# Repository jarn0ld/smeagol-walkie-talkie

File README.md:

smeagol-walkie-talkie
=====================

Welcome to Audio Group of SMEAGOL Project 2014 the Small, Embedded, Advanced and Generic Objects Laboratory at RWTH Aachen University. 

## Introduction ##

The goal of this project is to stream voice over a radio link. This includes voice recording, voice transmission and playback.
As radio nodes telosb´s needed to be used. This nodes are pretty power full battery powered devices including a micro-controller, a 2.4GHz radio transceiver and some sensors. 

## Hardware ##

Besides the two telosb´s some hardware was required to condition the microphone signal and to amplifie the output signal so that it can be used to drive earphones or a speaker.

### Microphone Amplifier ###

To generate electrical signals out out of sound waves a microphone is needed. For our purposes a electret microphone is right choice because of its small dimensions, its small price and
its good usability. However, the electrical signal generated by the microphone is ways to small for the telosb`s ADC. Therefore, the signal needs to be amplified to match up with the dynamic range
of the ADC. In order to do so we used an OpAmp as an amplifier in negative feedback configuration.  However before amplification the microphone needs to be biased through resistor R1. After amplification it is important to introduce a band limitation in order to satisfy Nyquist's theorem.
Therefore, a low pass is formed by R4 and C4 with a cut cuff below 4kHz.

#### Things to Notice ####
As this board circuit will be mounted directly beneath the transmitting node it is very important to be aware of the radio interference. Therefore, a proper ground plane is a must have, signal lines should be as short as possible and all supply pins should be closely decoupled.   

### Audio Amplifier ###

## Software ##
The program reads the ADC input (10 kHz and 12 bit) and send it over the radio using the CC2420 (RF chip). Afterwards, the sent samples are outputted at the DAC on the receiver seide.

Data flow of the samples:

Sender: ADC->DMA->Buffer->CC2420

Receiver: CC2420->Buffer->DMA->DAC

The code consists of 5 main components:

adc.c and dac.c:

- handles the initialization of the ADC/DAC using a timer

- sampling rate: 10 kHz, 12 bit

dma.c:

- configures the DMA Controller to interact with the ADC/DAC.

- includes the interrupts that are triggered, when a sample buffer was completely filled or outputted

rf.c:

- handles the initialization of the SPI interface, which is required to communite with the CC2420

- initializes the CC2420 (configuring registers)
		 - handles the sending and receiving of packets

main.c:

- puts all components together

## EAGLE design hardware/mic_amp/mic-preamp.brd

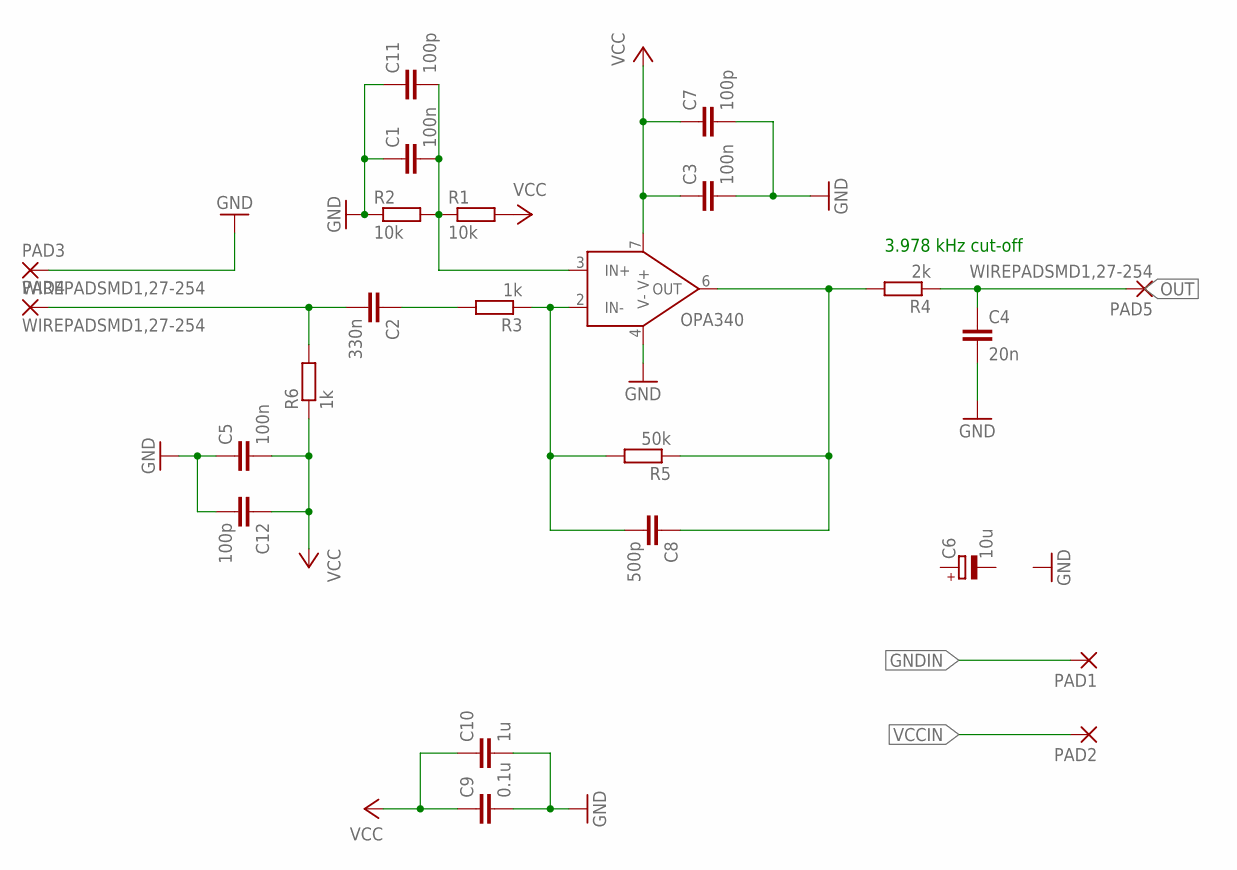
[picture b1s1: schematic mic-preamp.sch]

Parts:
C1, C3, C5: 100n; C0805
C2: 330n; C0805
C4: 20n; C0805
C6: 10u; E2,5-6E
C7, C11, C12: 100p; C0805
C8: 500p; C0805
C9: 0.1u; C0805
C10: 1u; C0805
OPA340: OPA340; DIL08
PAD1, PAD2: WIREPADSMD2,54-5,08; SMD2,54-5,08
PAD3, PAD4, PAD5: WIREPADSMD1,27-254; SMD1,27-2,54
R1, R2: 10k; R0805
R3, R6: 1k; R0805
R4: 2k; R0805
R5: 50k; R0805

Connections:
GND: C1.1, C3.2, C4.2, C5.1, C7.2, C9.2, C10.2, C11.1, C12.2, OPA340.4 (V-), PAD3.1, R2.1
GNDIN: PAD1.1
MIC: C2.2, PAD4.1, R6.2
unnamed: C8.1, OPA340.6 (OUT), R4.2, R5.1
unnamed: C1.2, C11.2, OPA340.3 (IN+), R1.1, R2.2
unnamed: C2.1, R3.2
unnamed: C8.2, OPA340.2 (IN-), R3.1, R5.2
OUT: C4.1, PAD5.1, R4.1
VCC: C3.1, C5.2, C7.1, C9.1, C10.1, C12.1, OPA340.7 (V+), R1.2, R6.1
VCCIN: PAD2.1

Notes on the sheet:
3.978 kHz cut-off

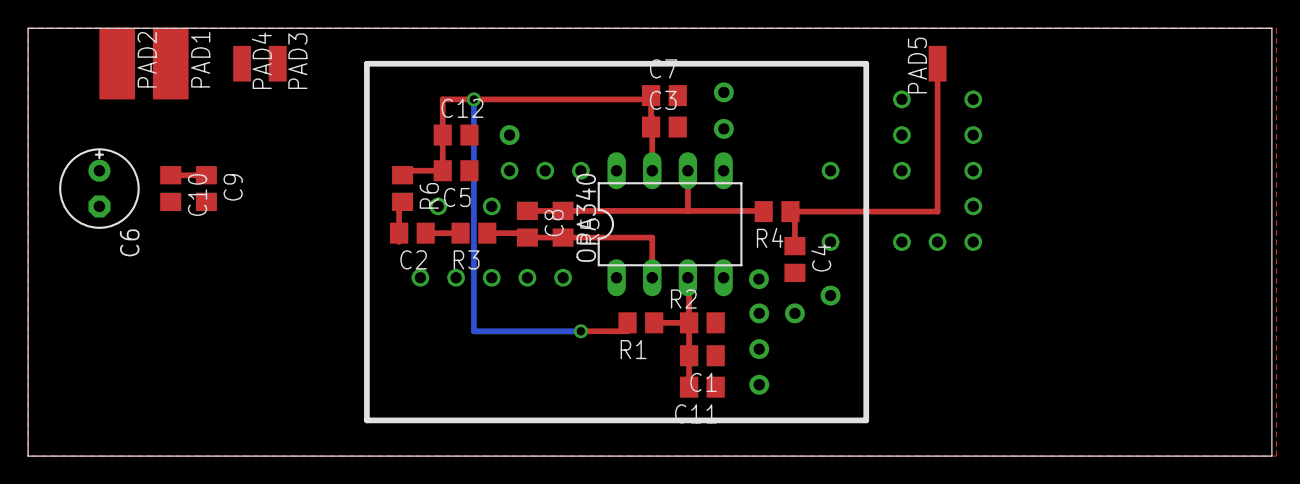
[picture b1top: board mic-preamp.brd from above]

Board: 2 copper layers, 88.6 x 30.5 mm, 24 parts (0 on the bottom side), 8 nets.

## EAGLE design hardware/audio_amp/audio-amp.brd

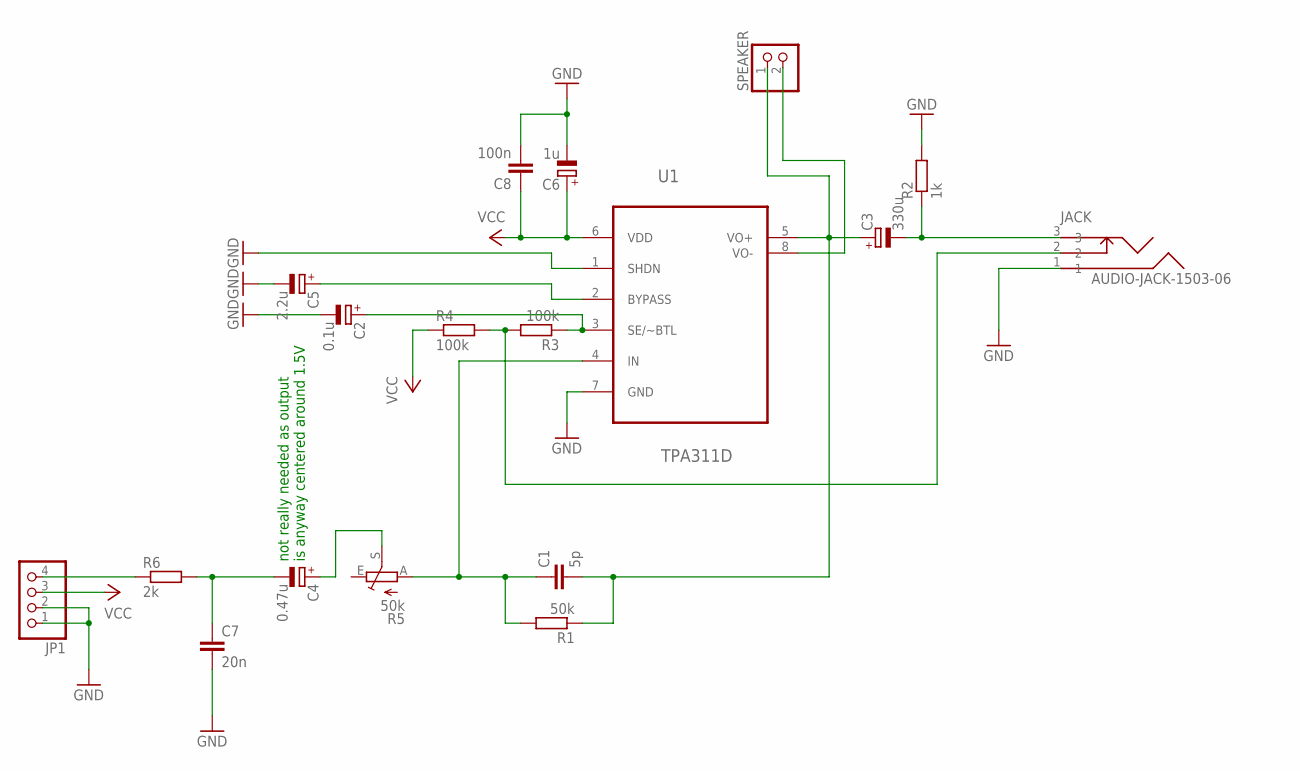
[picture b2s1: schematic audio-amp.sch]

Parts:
C1: 5p; C0805
C2: 0.1u; E2-5
C3: 330u; E2-5
C4: 0.47u; E2-5
C5: 2.2u; E2-5
C6: 1u; E2-5
C7: 20n; C0805
C8: 100n; C0805
JACK: AUDIO-JACK-1503-06; AUDIO-JACK
JP1: PINHD-1X4; 1X04
R1: 50k; R0805
R2: 1k; R0805
R3, R4: 100k; R0805
R5: 50k; PT-10
R6: 2k; R0805
SPEAKER: PINHD-1X2; 1X02
U1: TPA311D; SOIC127P600X175-8N

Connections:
GND: C2.-, C5.-, C6.-, C7.2, C8.2, JACK.1, JP1.1, JP1.2, R2.2, U1.1 (SHDN), U1.7 (GND)
unnamed: C1.2, C3.+, R1.1, SPEAKER.1, U1.5 (VO+)
unnamed: C3.-, JACK.3, R2.1
unnamed: JACK.2, R3.2, R4.2
unnamed: C2.+, R3.1, U1.3 (SE/~BTL)
unnamed: C1.1, R1.2, R5.A, U1.4 (IN)
unnamed: JP1.4, R6.1
unnamed: C5.+, U1.2 (BYPASS)
unnamed: C4.-, C7.1, R6.2
unnamed: SPEAKER.2, U1.8 (VO-)
unnamed: C4.+, R5.S
VCC: C6.+, C8.1, JP1.3, R4.1, U1.6 (VDD)

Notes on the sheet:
not really needed as output is anyway centered around 1.5V

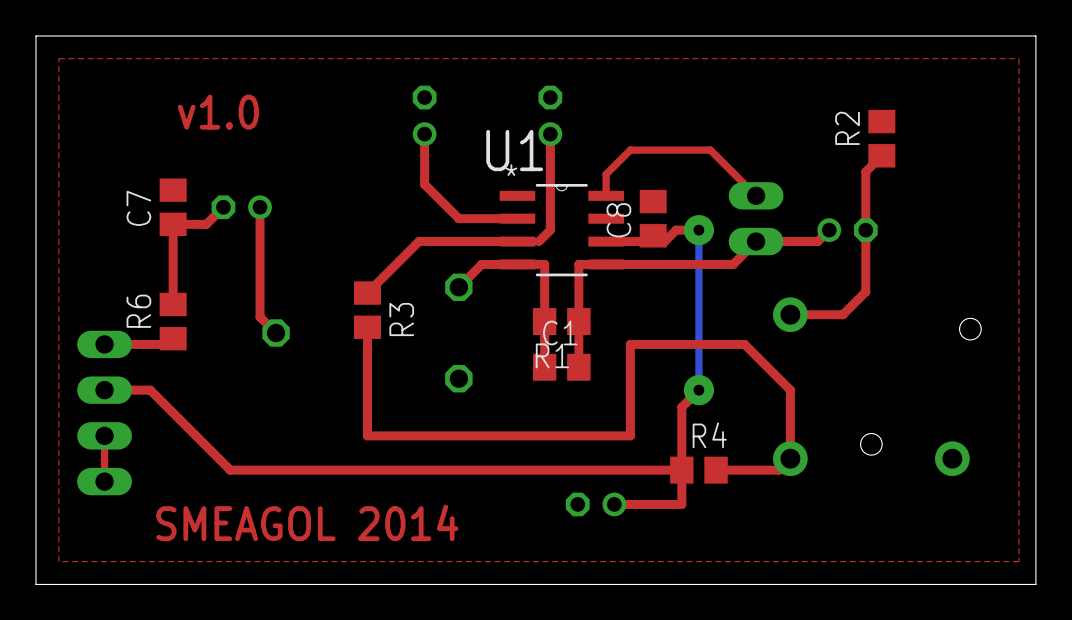
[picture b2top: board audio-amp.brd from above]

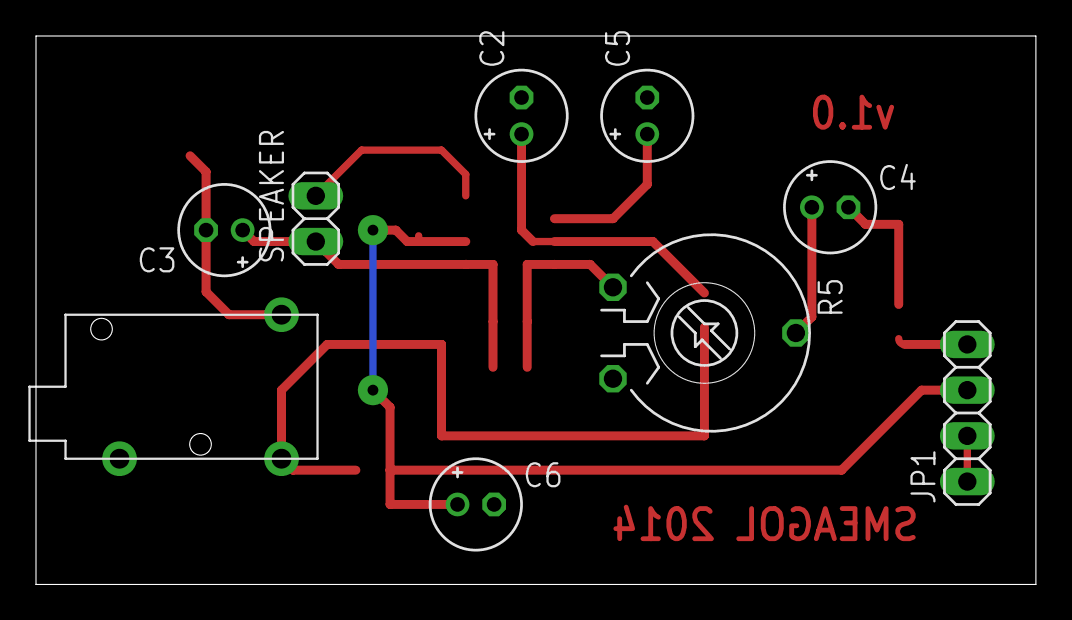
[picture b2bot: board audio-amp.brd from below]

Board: 2 copper layers, 55.6 x 30.5 mm, 18 parts (9 on the bottom side), 12 nets.

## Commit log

2014-06-28 description modified
2014-06-28 desc
2014-06-28 Create gh-pages branch via GitHub
2014-07-01 measurement data of mic-amp added
2014-07-01 modified mic-amp for better noise immunity
2014-07-01 Addes source files
2014-07-08 presentation added
2014-07-10 Added Readme and License
2014-07-10 Removec ihex firmware
2014-07-10 Added license to source files
2014-07-13 Because Keynote
2014-07-16 presentation recreated
2014-07-17 Added pipeline picture
2014-07-17 Added software to readme
2014-07-17 Readme formatting
2014-07-17 More README formatting
